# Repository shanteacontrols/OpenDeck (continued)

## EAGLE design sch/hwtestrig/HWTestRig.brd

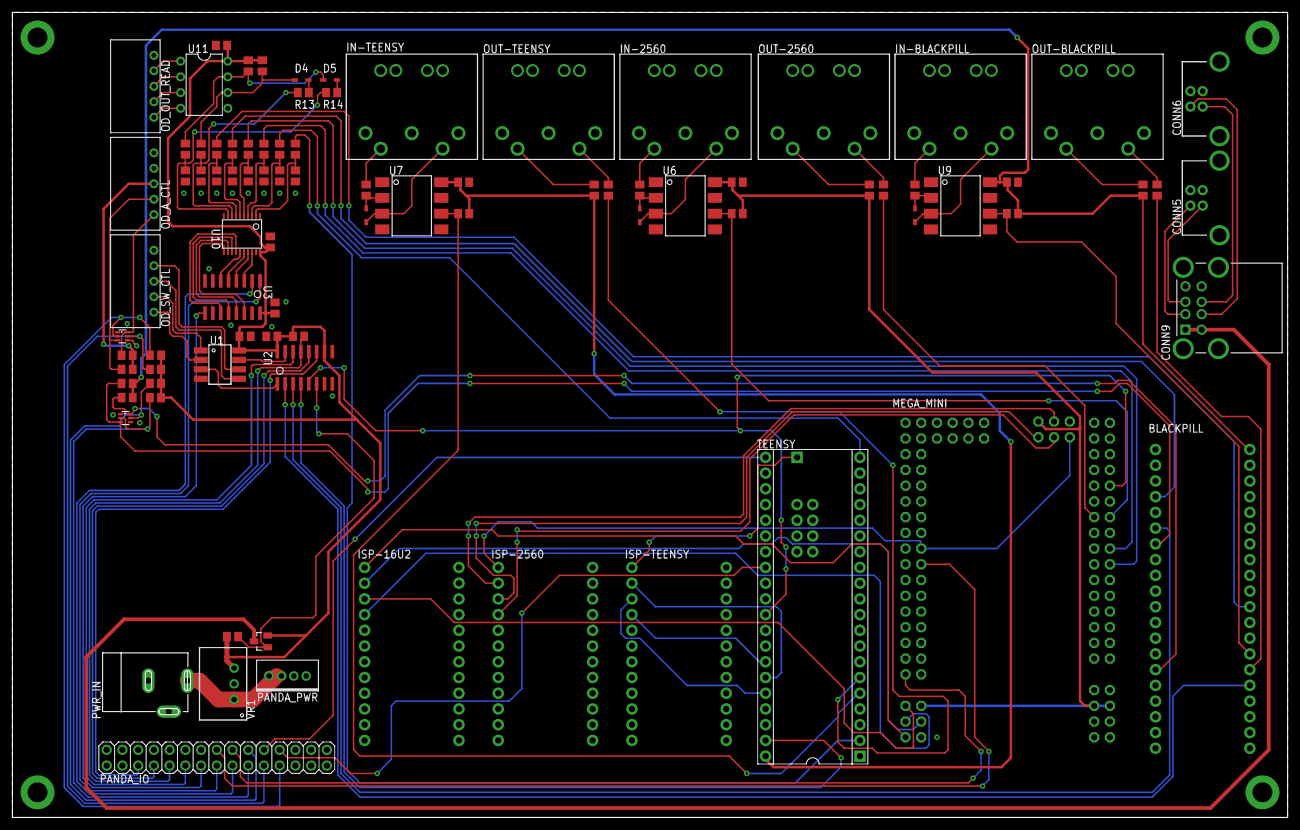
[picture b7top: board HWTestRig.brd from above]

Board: 2 copper layers, 206.0 x 130.0 mm, 88 parts (0 on the bottom side), 105 nets.

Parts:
BLACKPILL: STM32F411-BLACK_PILL
C1, C2, C3, C4, C5, C6, C7, C8, C9, C10, C11, C12, C13, C14, C15, C18: 100n; C0805
CONN5, CONN6: USB-B-H; USB-B-PTH
CONN9: USB-DUAL; SS-52100-003
D1, D2, D3, D4, D5: SOD-323
IN-2560: MIDI_CONN-STD; DIN5
IN-BLACKPILL: MIDI_CONN-STD; DIN5
IN-TEENSY: MIDI_CONN-STD; DIN5
ISP-16U2, ISP-2560: ARDUINO-PRO_MICRO
ISP-TEENSY: ARDUINO-PRO_MICRO
MEGA_MINI: ARDUINO-MEGA2560-MEDUINO
OD_A_CTL: PINHD-1X05-JST-XH-H; JST-XH-05P-H
OD_OUT_READ: PINHD-1X05-JST-XH-H; JST-XH-05P-H
OD_SW_CTL: PINHD-1X05-JST-XH-H; JST-XH-05P-H
OUT-2560: MIDI_CONN-STD; DIN5
OUT-BLACKPILL: MIDI_CONN-STD; DIN5
OUT-TEENSY: MIDI_CONN-STD; DIN5
PANDA_IO: PINHD-2X15; 2X15-2.54
PANDA_PWR: PINHD-1X04-SMW-TH-2MM-V; SMW200-04P
PWR_IN: BARREL_JACK
Q2: BSS314PEH6327XTSA1; SOT23
Q3, Q4: BSS138PS; SOT-363
R1, R4, R7, R15, R16, R33, R34: 10k; R0805
R2, R3, R5, R6, R10, R11, R12: 220; R0805
R8: 33; R0805
R9: 10; R0805
R13, R14: 100; R0805
R17, R18, R19, R20, R21, R22, R23, R24: 200k; R0805
R25, R26, R27, R28, R29, R30, R31, R32: 4.7k; R0805
TEENSY: TEENSY-2.0++
U1: TC7W66FU; SM8
U2: 74HC595-SO16; SO16
U3: 74HC165; SO16
U6, U7, U9: 6N137-SMD; SMD-8
U10: 74AHC541; TSSOP20
U11: VO2631; DIL08
VR1: TSR-1-2450

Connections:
+3V3_BP: BLACKPILL.P1.20, C2.2, R7.1, R8.2, R29.2, R32.2, U9.8
+3V3_OD2: OD_A_CTL.3, R25.2, R28.2
+5V: C3.1, C4.1, C5.1, C6.1, C18.1, Q2.2, R15.2, R16.2, R26.2, R27.2, R30.2, R31.2, R33.2, R34.1, U1.8, U2.10, U2.16, U3.16, U10.20, U11.8, VR1.3
+5V_HUB: CONN9.VBUS1, CONN9.VBUS2, Q2.3
+5V_MEGA2560: C15.2, MEGA_MINI.+5V, MEGA_MINI.+5V1, MEGA_MINI.+5V2, MEGA_MINI.+5V3, R4.1, R10.2, U6.8
+5V_TEENSY: C1.2, R1.1, R2.2, TEENSY.VCC, U7.8
+12V: PANDA_PWR.1, PANDA_PWR.2, PWR_IN.PWR1, VR1.1
ANALOG_CTL_BLACKPILL_1_3V: BLACKPILL.P2.6, Q3.6, R29.1
ANALOG_CTL_BLACKPILL_1_5V: PANDA_IO.19, Q3.2, R30.1
ANALOG_CTL_BLACKPILL_2_3V: BLACKPILL.P2.14, Q3.3, R32.1
ANALOG_CTL_BLACKPILL_2_5V: PANDA_IO.20, Q3.5, R31.1
ANALOG_CTL_MEGA2560_1: MEGA_MINI.A15, PANDA_IO.16
ANALOG_CTL_MEGA2560_2: MEGA_MINI.A0, PANDA_IO.18
ANALOG_CTL_OD2_1_3V: OD_A_CTL.1, Q4.6, R25.1
ANALOG_CTL_OD2_1_5V: PANDA_IO.23, Q4.2, R26.1
ANALOG_CTL_OD2_2_3V: OD_A_CTL.2, Q4.3, R28.1
ANALOG_CTL_OD2_2_5V: PANDA_IO.21, Q4.5, R27.1
ANALOG_CTL_TEENSY_1: PANDA_IO.24, TEENSY.PF0
ANALOG_CTL_TEENSY_2: PANDA_IO.22, TEENSY.PF7
GND: BLACKPILL.P1.19, BLACKPILL.P2.2, C1.1, C2.1, C3.2, C4.2, C5.2, C6.2, C7.1, C8.1, C9.1, C10.1, C11.1, C12.1, C13.1, C14.1, C15.1, C18.2, CONN5.GND, CONN5.S1, CONN5.S2, CONN6.GND, CONN6.S1, CONN6.S2, CONN9.GND1, CONN9.GND2, CONN9.S1, CONN9.S2, CONN9.S3, CONN9.S4, ISP-16U2.3, ISP-16U2.4, ISP-16U2.23, ISP-2560.3, ISP-2560.4, ISP-2560.23, ISP-TEENSY.3, ISP-TEENSY.4, ISP-TEENSY.23, MEGA_MINI.GND, MEGA_MINI.GND1, MEGA_MINI.GND2, MEGA_MINI.GND3, MEGA_MINI.GND4, MEGA_MINI.GND5, OD_A_CTL.4, OD_A_CTL.5, OD_OUT_READ.5, OD_SW_CTL.5, OUT-2560.2, OUT-BLACKPILL.2, OUT-TEENSY.2, PANDA_IO.1, PANDA_IO.3, PANDA_PWR.3, PANDA_PWR.4, PWR_IN.GND@1, PWR_IN.GND@2, Q3.1, Q3.4, Q4.1, Q4.4, TEENSY.GND, TEENSY.GND1, U1.4, U2.8, U3.8, U3.15, U6.5, U7.5, U9.5, U10.1, U10.10, U10.19, U11.5, VR1.2
MIDI_IN_1: D2.A, IN-TEENSY.5, U7.3
MIDI_IN_2: IN-TEENSY.4, R6.1
MIDI_IN_3: D3.A, IN-BLACKPILL.5, U9.3
MIDI_IN_4: IN-2560.4, R5.1
MIDI_IN_5: D1.A, IN-2560.5, U6.3
MIDI_IN_6: IN-BLACKPILL.4, R11.1
MIDI_IN_2560: MEGA_MINI.19, R4.2, U6.6
MIDI_IN_BLACKPILL: BLACKPILL.P1.7, R7.2, U9.6
MIDI_IN_DIODE_OUT: D1.C, R5.2, U6.2
MIDI_IN_DIODE_OUT1: D2.C, R6.2, U7.2
MIDI_IN_DIODE_OUT2: D3.C, R11.2, U9.2
MIDI_IN_TEENSY: R1.2, TEENSY.PD2, U7.6
MIDI_OUT_1: OUT-TEENSY.4, R2.1
MIDI_OUT_2: OUT-TEENSY.5, R3.1
MIDI_OUT_3: OUT-BLACKPILL.4, R8.1
MIDI_OUT_4: OUT-2560.4, R10.1
MIDI_OUT_5: OUT-2560.5, R12.1
MIDI_OUT_6: OUT-BLACKPILL.5, R9.1
MIDI_OUT_2560: MEGA_MINI.18, R12.2
MIDI_OUT_BLACKPILL: BLACKPILL.P1.6, R9.2
MIDI_OUT_TEENSY: R3.2, TEENSY.PD3
MISO_16U2: ISP-16U2.15, MEGA_MINI.MISO_16U2
MISO_2560: ISP-2560.15, MEGA_MINI.MISO_2560
MISO_TEENSY: ISP-TEENSY.15, TEENSY.PB3
MOSI_16U2: ISP-16U2.14, MEGA_MINI.MOSI_16U2
MOSI_2560: ISP-2560.14, MEGA_MINI.MOSI_2560
MOSI_TEENSY: ISP-TEENSY.14, TEENSY.PB2
unnamed: D4.A, R13.1
unnamed: D5.A, R14.1
OUT_READ_2560_1: MEGA_MINI.15, R19.1
OUT_READ_2560_1_BUF: C9.2, R19.2, U10.4
OUT_READ_2560_1_DEB: U3.5, U10.16
OUT_READ_2560_2: MEGA_MINI.13, R20.1
OUT_READ_2560_2_BUF: C10.2, R20.2, U10.5
OUT_READ_2560_2_DEB: U3.6, U10.15
OUT_READ_BLACKPILL_1: BLACKPILL.P1.10, R24.1
OUT_READ_BLACKPILL_1_BUF: C14.2, R24.2, U10.7
OUT_READ_BLACKPILL_1_DEB: U3.12, U10.13
OUT_READ_BLACKPILL_2: BLACKPILL.P2.17, R23.1
OUT_READ_BLACKPILL_2_BUF: C13.2, R23.2, U10.6
OUT_READ_BLACKPILL_2_DEB: U3.11, U10.14
OUT_READ_OD2_1: D5.C, R18.1, R33.1, U11.7
OUT_READ_OD2_1_BUF: C8.2, R14.2, R18.2, U10.9
OUT_READ_OD2_1_C: OD_OUT_READ.3, U11.2
OUT_READ_OD2_1_DEB: U3.14, U10.11
OUT_READ_OD2_1_R: OD_OUT_READ.4, U11.1
OUT_READ_OD2_2: D4.C, R17.1, R34.2, U11.6
OUT_READ_OD2_2_BUF: C7.2, R13.2, R17.2, U10.8
OUT_READ_OD2_2_C: OD_OUT_READ.2, U11.3
OUT_READ_OD2_2_DEB: U3.13, U10.12
OUT_READ_OD2_2_R: OD_OUT_READ.1, U11.4
OUT_READ_TEENSY_1: R21.1, TEENSY.PB7
OUT_READ_TEENSY_1_BUF: C11.2, R21.2, U10.2
OUT_READ_TEENSY_1_DEB: U3.3, U10.18
OUT_READ_TEENSY_2: R22.1, TEENSY.PC7
OUT_READ_TEENSY_2_BUF: C12.2, R22.2, U10.3
OUT_READ_TEENSY_2_DEB: U3.4, U10.17
PWR_CTL: Q2.1, R15.1, U2.6
RESET_16U2: ISP-16U2.13, MEGA_MINI.RST_16U2
RESET_2560: ISP-2560.13, MEGA_MINI.RESET, MEGA_MINI.RESET@1
RESET_TEENSY: ISP-TEENSY.13, TEENSY.RST
SCK_16U2: ISP-16U2.16, MEGA_MINI.SCK_16U2
SCK_2560: ISP-2560.16, MEGA_MINI.SCK_2560
SCK_TEENSY: ISP-TEENSY.16, TEENSY.PB1
SR_DATA_OUT: PANDA_IO.11, U2.14
SR_IN_CLOCK: PANDA_IO.17, U3.2
SR_IN_DATA: PANDA_IO.13, U3.9
SR_IN_LATCH: PANDA_IO.15, U3.1
SR_OUT_CLOCK: PANDA_IO.5, U2.11
SR_OUT_ENABLE: PANDA_IO.9, R16.1, U2.13
SR_OUT_LATCH: PANDA_IO.7, U2.12
SW_CTL_AVR_1: TEENSY.PB6, U2.4
SW_CTL_AVR_2: MEGA_MINI.23, TEENSY.PE6, U2.5
SW_CTL_BLACKPILL_1: BLACKPILL.P2.15, U2.3
SW_CTL_BLACKPILL_2: BLACKPILL.P1.5, U2.2
SW_CTL_OD2_1: U1.7, U2.15
SW_CTL_OD2_2: U1.3, U2.1
SW_OD2_1_IN: OD_SW_CTL.2, U1.1
SW_OD2_1_OUT: OD_SW_CTL.1, U1.2
SW_OD2_2_IN: OD_SW_CTL.3, U1.5
SW_OD2_2_OUT: OD_SW_CTL.4, U1.6
USB_D+_HUB1: CONN5.D+, CONN9.D+1
USB_D+_HUB2: CONN6.D+, CONN9.D+2
USB_D-_HUB1: CONN5.D-, CONN9.D-1
USB_D-_HUB2: CONN6.D-, CONN9.D-2
